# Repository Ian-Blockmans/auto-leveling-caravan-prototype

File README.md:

# auto leveling caravan
prototype met een stm32 controller. prototype werkt maar het is geen afgewerkt product

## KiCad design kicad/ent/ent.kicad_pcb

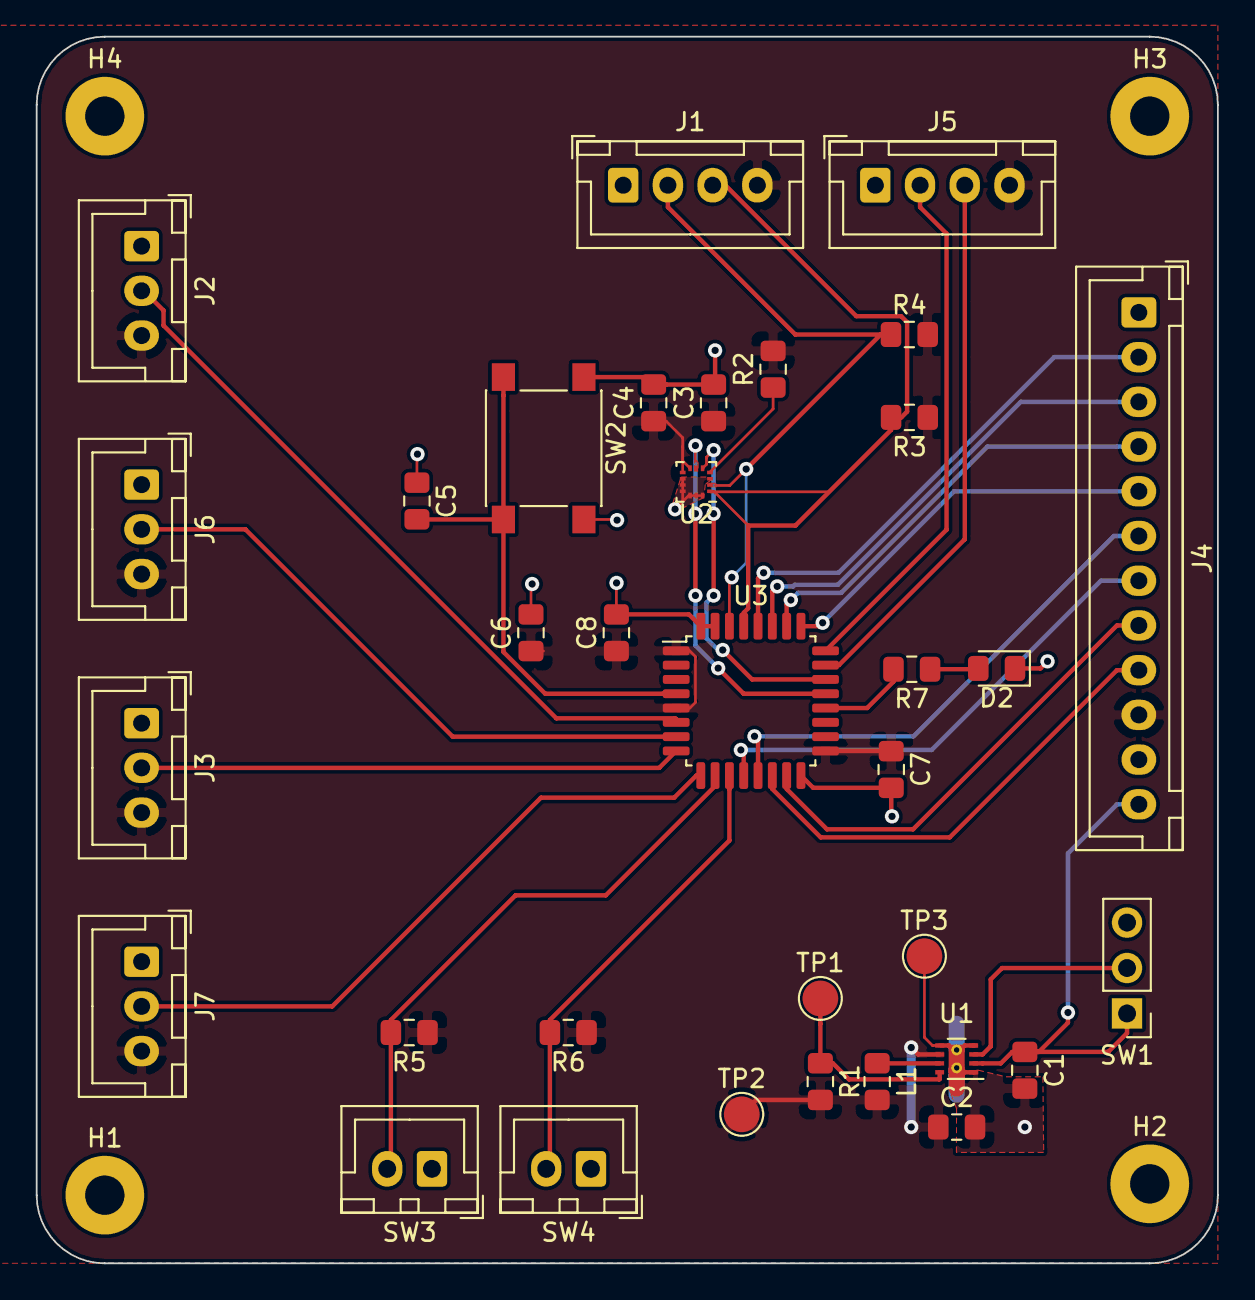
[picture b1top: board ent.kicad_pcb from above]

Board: 2 copper layers, 66.0 x 68.6 mm, 38 parts (0 on the bottom side), 30 nets.

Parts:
C1, C3: 10µ; C_0805_2012Metric_Pad1.15x1.40mm_HandSolder
C2: 22µf; C_0805_2012Metric_Pad1.15x1.40mm_HandSolder
C4, C7, C8: 100n; C_0805_2012Metric_Pad1.15x1.40mm_HandSolder
C5: 100nF; C_0805_2012Metric_Pad1.15x1.40mm_HandSolder
C6: 4.7µ; C_0805_2012Metric_Pad1.15x1.40mm_HandSolder
D2: LED; LED_0805_2012Metric_Pad1.15x1.40mm_HandSolder
H1, H2, H3, H4: MountingHole_Pad; MountingHole_2.2mm_M2_Pad
J1, J5: Conn_01x04_Male; JST_XH_B4B-XH-A_1x04_P2.50mm_Vertical
J2, J3, J6, J7: Conn_01x03_Male; JST_XH_B3B-XH-A_1x03_P2.50mm_Vertical
J4: Conn_01x12_Male; JST_XH_B12B-XH-A_1x12_P2.50mm_Vertical
L1: 2.2µH; L_0805_2012Metric_Pad1.15x1.40mm_HandSolder
R1: 100k; R_0805_2012Metric_Pad1.15x1.40mm_HandSolder
R2, R3, R4, R5, R6: 10k; R_0805_2012Metric_Pad1.15x1.40mm_HandSolder
R7: R_Small; R_0805_2012Metric_Pad1.15x1.40mm_HandSolder
SW1: SW_SPDT; PinHeader_1x03_P2.54mm_Vertical
SW2: SW_Push; SW_SPST_PTS645
SW3, SW4: SW_Push; JST_XH_B2B-XH-A_1x02_P2.50mm_Vertical
TP1, TP2, TP3: TestPoint; TestPoint_Pad_D2.0mm
U1: TPS62172DSG; WSON-8-1EP_2x2mm_P0.5mm_EP0.9x1.6mm_ThermalVias
U2: LIS2DHTR; LGA-14_2x2mm_P0.35mm_LayoutBorder3x4y
U3: STM32F030K6Tx; LQFP-32_7x7mm_P0.8mm

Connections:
+12V: C1.1, J4.12, SW1.1, U1.2
Extend: R5.2, SW3.2, U3.10
GND: C1.2, C2.2, C3.2, C4.2, C5.1, C6.2, C7.2, C8.2, D2.1, H1.1, H2.1, H3.1, H4.1, J1.1, J2.1, J3.1, J4.1, J4.11, J5.1, J6.1, J7.1, SW1.3, SW2.1, SW3.1, SW4.1, TP3.1, U1.1, U1.4, U1.5, U1.9, U2.3, U2.9, U2.10, U2.11, U2.12, U2.13, U2.14, U3.16, U3.31, U3.32
INT1: U2.6, U3.21
INT2: U2.5, U3.22
LED: R7.2, U3.20
NSS1: J4.9, U3.14
NSS2: J4.8, U3.15
NSS3: J4.7, U3.12
NSS4: J4.6, U3.13
unnamed: C5.2, SW2.2, U3.4
unnamed: D2.2, R7.1
unnamed: J1.2, R4.1, U2.2, U3.30
unnamed: J1.3, R3.2, U2.1, U3.29
unnamed: J4.5, U3.25
unnamed: L1.1, U1.7
unnamed: R1.1, TP1.1, U1.8
unnamed: R2.1, U2.4
unnamed: SW1.2, U1.3
Retract: R6.2, SW4.2, U3.11
SPI1_MISO: J4.3, U3.27
SPI1_MOSI: J4.2, U3.28
SPI1_SCK: J4.4, U3.26
STOP1: J2.2, U3.6
STOP2: J6.2, U3.7
STOP3: J3.2, U3.8
STOP4: J7.2, U3.9
SWCLK: J5.2, U3.24
SWDIO: J5.3, U3.23
VOS: C2.1, C3.1, C4.1, C6.1, C7.1, C8.1, J1.4, J2.3, J3.3, J4.10, J5.4, J6.3, J7.3, L1.2, R1.2, R2.2, R3.1, R4.2, R5.1, R6.1, TP2.1, U1.6, U2.7, U2.8, U3.1, U3.5, U3.17

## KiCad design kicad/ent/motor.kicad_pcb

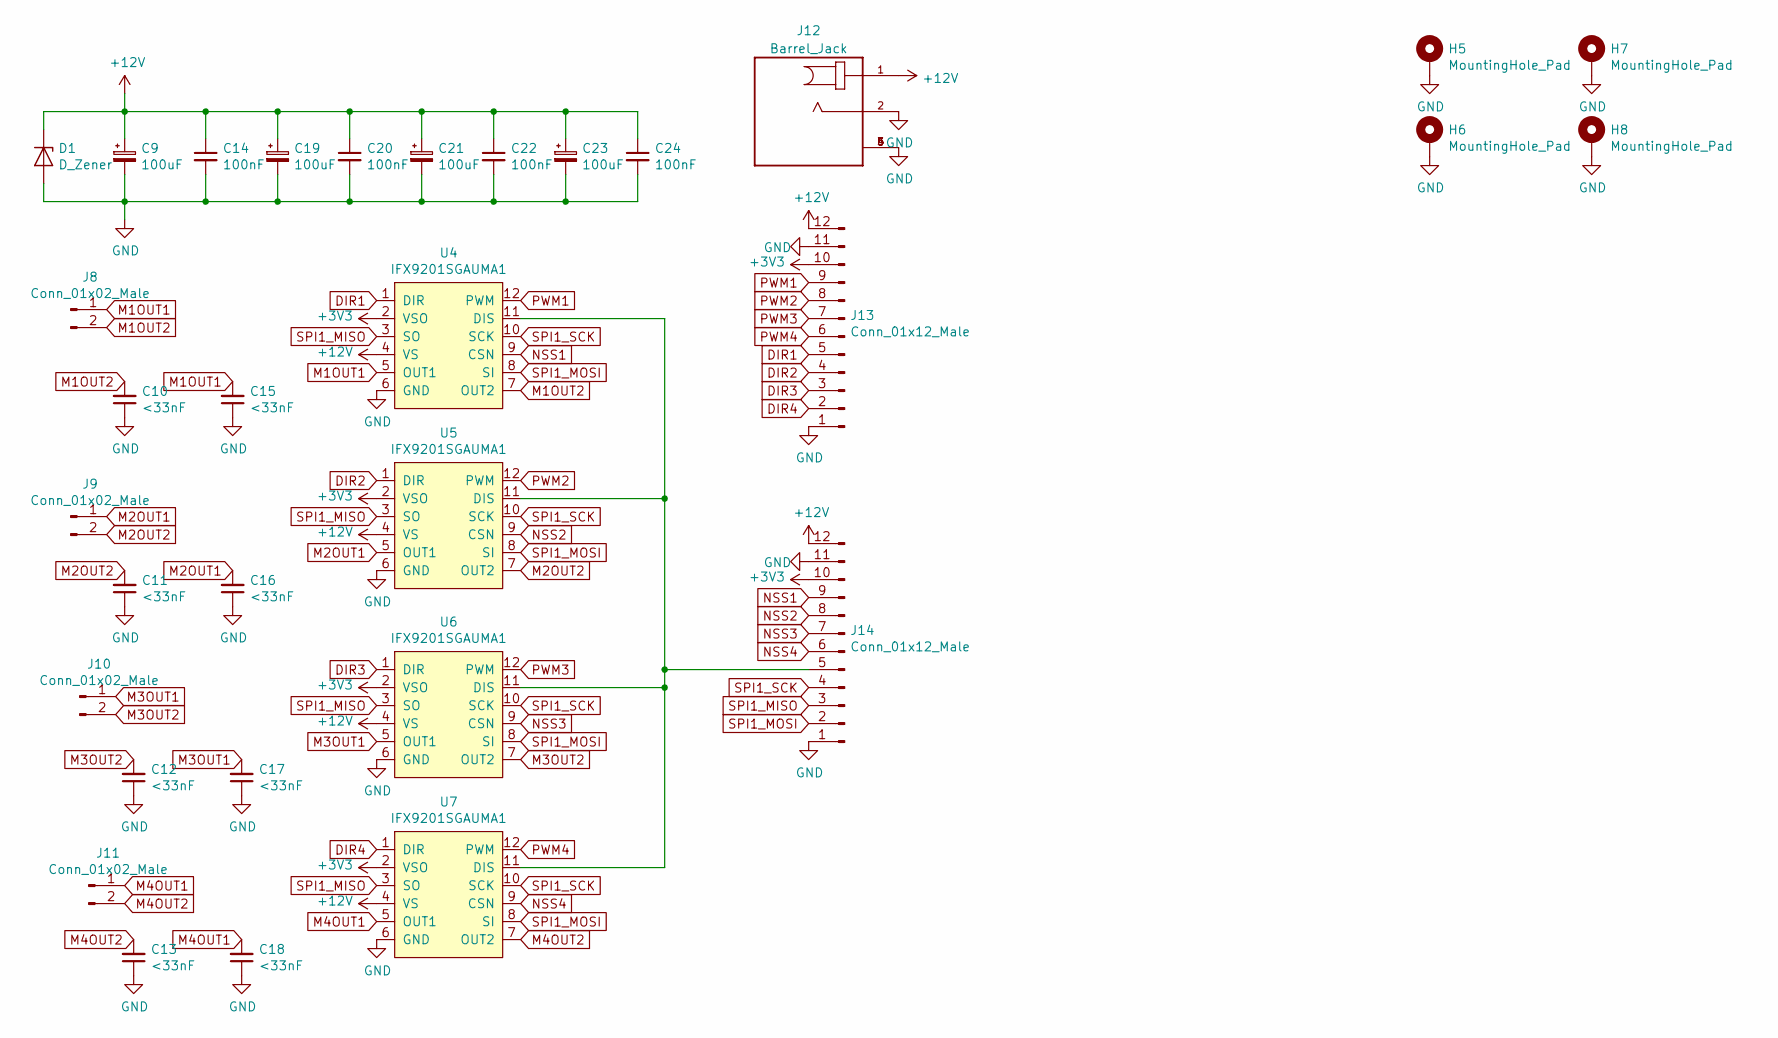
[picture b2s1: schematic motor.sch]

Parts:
C9, C19, C21, C23: 100uF; CP_Radial_D8.0mm_P3.50mm
C10, C11, C12, C13, C15, C16, C17, C18: <33nF; C_0805_2012Metric_Pad1.15x1.40mm_HandSolder
C14, C20, C22, C24: 100nF; C_0805_2012Metric_Pad1.15x1.40mm_HandSolder
D1: D_Zener; D_SOD-323_HandSoldering
H5, H6, H7, H8: MountingHole_Pad; MountingHole_2.2mm_M2_Pad
J8, J9, J10, J11: Conn_01x02_Male; JST_SFH_SM02B-SFHRS-TF_1x02-1MP_P4.20mm_Horizontal
J12: Barrel_Jack; CUI_PJ-082BH
J13, J14: Conn_01x12_Male; JST_XH_B12B-XH-A_1x12_P2.50mm_Vertical
U4, U5, U6, U7: IFX9201SGAUMA1; PG-DSO-12-17

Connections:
+12V: C9.1, C14.1, C19.1, C20.1, C21.1, C22.1, C23.1, C24.1, D1.1 (K), J12.1, J13.12, J14.12, U4.4 (VS), U5.4 (VS), U6.4 (VS), U7.4 (VS)
DIR1: J13.5, U4.1 (DIR)
DIR2: J13.4, U5.1 (DIR)
DIR3: J13.3, U6.1 (DIR)
DIR4: J13.2, U7.1 (DIR)
GND: C9.2, C10.1, C11.1, C12.1, C13.1, C14.2, C15.1, C16.1, C17.1, C18.1, C19.2, C20.2, C21.2, C22.2, C23.2, C24.2, D1.2 (A), H5.1, H6.1, H7.1, H8.1, J12.2, J12.3 (SHIELD), J12.4 (SHIELD), J12.5 (SHIELD), J12.6 (SHIELD), J12.7, J13.1, J13.11, J14.1, J14.11, U4.6 (GND), U4.13, U5.6 (GND), U5.13, U6.6 (GND), U6.13, U7.6 (GND), U7.13
M1OUT1: C15.2, J8.1, U4.5 (OUT1)
M1OUT2: C10.2, J8.2, U4.7 (OUT2)
M2OUT1: C16.2, J9.1, U5.5 (OUT1)
M2OUT2: C11.2, J9.2, U5.7 (OUT2)
M3OUT1: C17.2, J10.1, U6.5 (OUT1)
M3OUT2: C12.2, J10.2, U6.7 (OUT2)
M4OUT1: C18.2, J11.1, U7.5 (OUT1)
M4OUT2: C13.2, J11.2, U7.7 (OUT2)
NSS1: J14.9, U4.9 (CSN)
NSS2: J14.8, U5.9 (CSN)
NSS3: J14.7, U6.9 (CSN)
NSS4: J14.6, U7.9 (CSN)
unnamed: J14.5, U4.11 (DIS), U5.11 (DIS), U6.11 (DIS), U7.11 (DIS)
PWM1: J13.9, U4.12 (PWM)
PWM2: J13.8, U5.12 (PWM)
PWM3: J13.7, U6.12 (PWM)
PWM4: J13.6, U7.12 (PWM)
SPI1_MISO: J14.3, U4.3 (SO), U5.3 (SO), U6.3 (SO), U7.3 (SO)
SPI1_MOSI: J14.2, U4.8 (SI), U5.8 (SI), U6.8 (SI), U7.8 (SI)
SPI1_SCK: J14.4, U4.10 (SCK), U5.10 (SCK), U6.10 (SCK), U7.10 (SCK)
VOS: J13.10, J14.10, U4.2 (VSO), U5.2 (VSO), U6.2 (VSO), U7.2 (VSO)

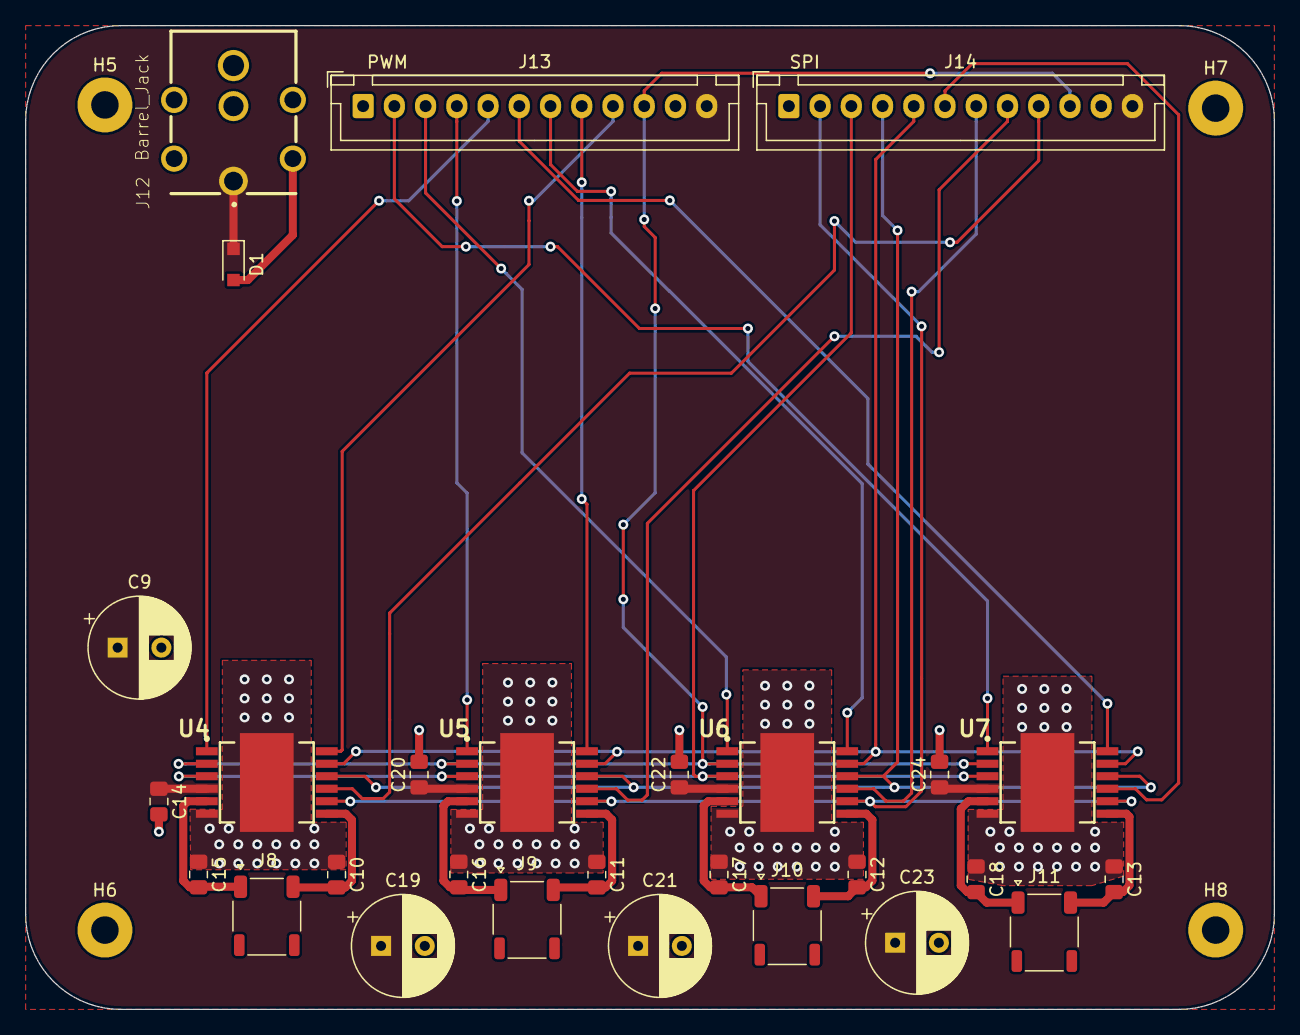
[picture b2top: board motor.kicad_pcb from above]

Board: 2 copper layers, 99.9 x 78.7 mm, 32 parts (0 on the bottom side), 27 nets.

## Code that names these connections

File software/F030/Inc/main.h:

/* USER CODE BEGIN Header */
/**
  ******************************************************************************
  * @file           : main.h
  * @brief          : Header for main.c file.
  *                   This file contains the common defines of the application.
  ******************************************************************************
  * @attention
  *
  * <h2><center>&copy; Copyright (c) 2020 STMicroelectronics.
  * All rights reserved.</center></h2>
  *
  * This software component is licensed by ST under BSD 3-Clause license,
  * the "License"; You may not use this file except in compliance with the
  * License. You may obtain a copy of the License at:
  *                        opensource.org/licenses/BSD-3-Clause
  *
  ******************************************************************************
  */
/* USER CODE END Header */

/* Define to prevent recursive inclusion -------------------------------------*/
#ifndef __MAIN_H
#define __MAIN_H

#ifdef __cplusplus
extern "C" {
#endif

/* Includes ------------------------------------------------------------------*/
#include "stm32f0xx_hal.h"

/* Private includes ----------------------------------------------------------*/
/* USER CODE BEGIN Includes */

/* USER CODE END Includes */

/* Exported types ------------------------------------------------------------*/
/* USER CODE BEGIN ET */

/* USER CODE END ET */

/* Exported constants --------------------------------------------------------*/
/* USER CODE BEGIN EC */

/* USER CODE END EC */

/* Exported macro ------------------------------------------------------------*/
/* USER CODE BEGIN EM */

/* USER CODE END EM */

void HAL_TIM_MspPostInit(TIM_HandleTypeDef *htim);

/* Exported functions prototypes ---------------------------------------------*/
void Error_Handler(void);

/* USER CODE BEGIN EFP */

/* USER CODE END EFP */

/* Private defines -----------------------------------------------------------*/
#define STOP1_Pin GPIO_PIN_0
#define STOP1_GPIO_Port GPIOA
#define STOP2_Pin GPIO_PIN_1
#define STOP2_GPIO_Port GPIOA
#define STOP3_Pin GPIO_PIN_2
#define STOP3_GPIO_Port GPIOA
#define STOP4_Pin GPIO_PIN_3
#define STOP4_GPIO_Port GPIOA
#define Extend_Pin GPIO_PIN_4
#define Extend_GPIO_Port GPIOA
#define Retract_Pin GPIO_PIN_5
#define Retract_GPIO_Port GPIOA
#define LED_Pin GPIO_PIN_10
#define LED_GPIO_Port GPIOA
#define INT2_Pin GPIO_PIN_11
#define INT2_GPIO_Port GPIOA
#define INT2A12_Pin GPIO_PIN_12
#define INT2A12_GPIO_Port GPIOA
/* USER CODE BEGIN Private defines */

/* USER CODE END Private defines */

#ifdef __cplusplus
}
#endif

#endif /* __MAIN_H */

/************************ (C) COPYRIGHT STMicroelectronics *****END OF FILE****/

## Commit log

2020-02-14 stert bestanden
2020-02-14 eclipse broll
2020-03-05 updated schema
2020-03-05 cleanup
2020-03-05 schema main done
2020-03-05 + motor drivers
2020-03-06 ignore fix
2020-03-06 Caps bij motor drivers
2020-03-06 footprints
    alles behalve power/motor connectors
2020-03-08 begin pcb
2020-03-10 soft update + pcb main try 1
2020-03-11 added interface buttons
    enkel schema
2020-03-14 pcb's
2020-03-16 barreljack footprint update
    naar de footprint van mouser veranderd
2020-03-16 pcb done
2020-03-16 gerbers
2020-05-05 software
    functioneel
2020-05-25 final code
2020-11-27 added video and images
